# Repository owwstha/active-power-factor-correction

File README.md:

## active power factor correction

### Overview & Objectives

The primary objective was to design a high-efficiency Active Power Factor Correction stage. Utilizing a PI control loop to modulate PWM signals, the system achieves a Power Factor (PF) > 0.99. Key design priorities included:
* Minimizing THD.
* Regulating the DC bus voltage against AC input fluctuations and sudden load transients.

---

### Technical Details

* **Control Architecture**: A dual-loop PI control system manages the feedback: a outer voltage PI loop stabilizes the DC bus output, while a fast inner current PI loop continuously adjusts the duty cycle of the PWM signal.
* **Power Stage**: A diode bridge rectifier converts the AC line voltage to unsmoothed DC, which is immediately fed into a high-frequency Boost Converter. The switched PWM controls the boost stage to shape the input current into a pure sinusoidal waveform aligned with the AC voltage.

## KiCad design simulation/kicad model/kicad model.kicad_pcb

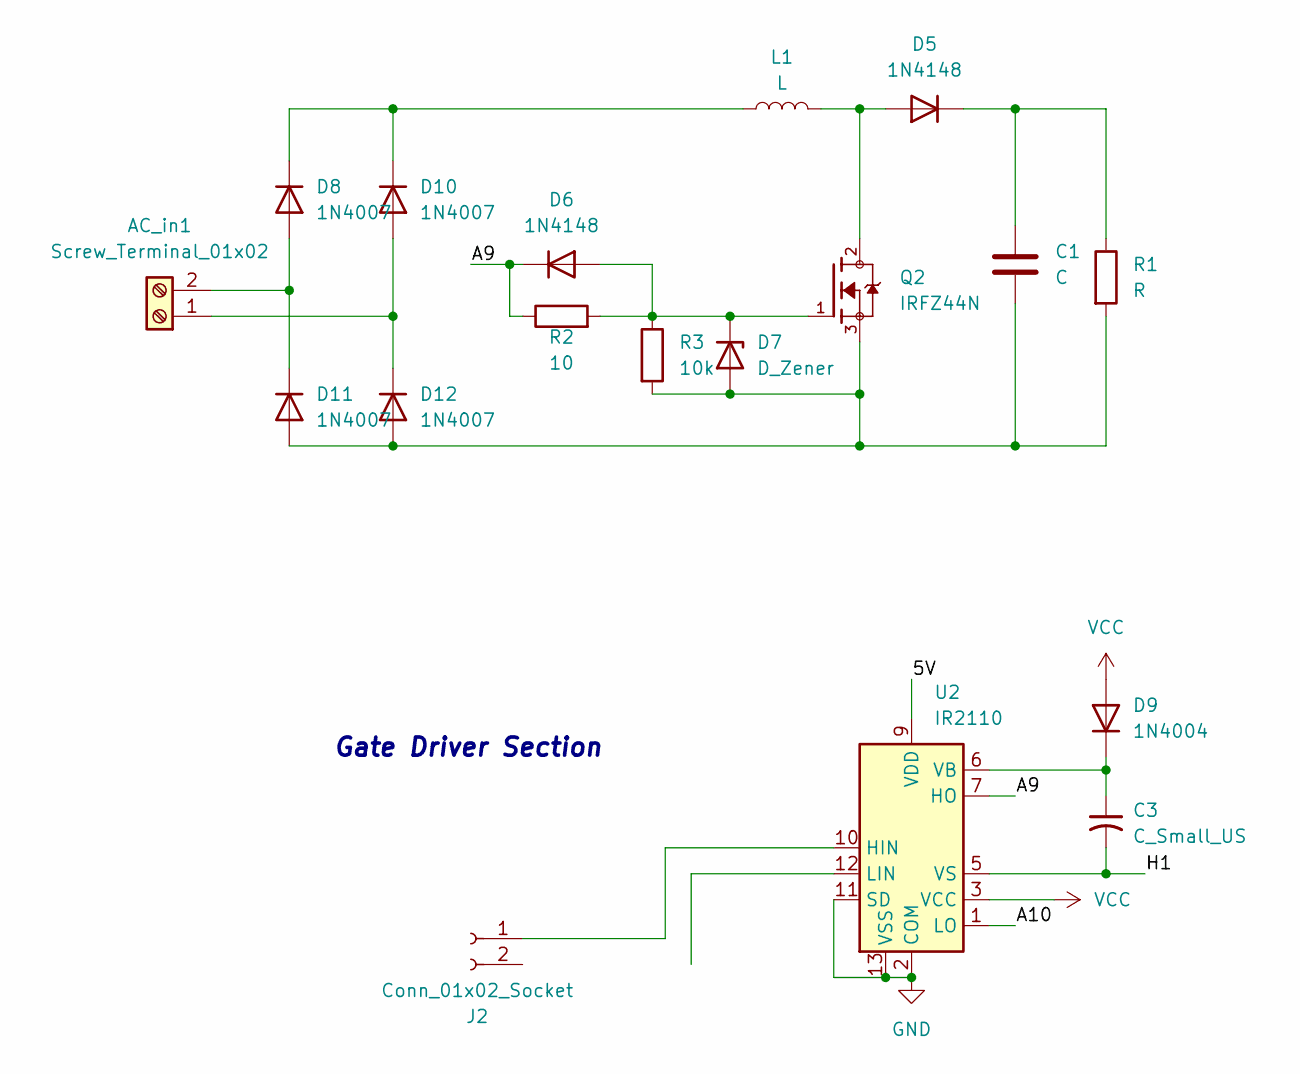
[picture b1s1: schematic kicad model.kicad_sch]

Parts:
AC_in1: Screw_Terminal_01x02; TerminalBlock_Xinya_XY308-2.54-2P_1x02_P2.54mm_Horizontal
C1: C; C_Radial_D6.3mm_H5.0mm_P2.50mm
C3: C_Small_US; C_Radial_D6.3mm_H7.0mm_P2.50mm
D5, D6: 1N4148; D_DO-35_SOD27_P7.62mm_Horizontal
D7: D_Zener; D_A-405_P7.62mm_Horizontal
D8, D10, D11, D12: 1N4007; D_DO-41_SOD81_P10.16mm_Horizontal
D9: 1N4004; D_A-405_P7.62mm_Horizontal
J2: Conn_01x02_Socket; PinHeader_1x01_P2.54mm_Vertical
L1: L; L_Axial_L5.3mm_D2.2mm_P10.16mm_Horizontal_Vishay_IM-1
Q2: IRFZ44N; TO-247-3_Vertical; PARTREV 09/21/10
R1: R; R_Axial_DIN0207_L6.3mm_D2.5mm_P10.16mm_Horizontal
R2: 10; R_Axial_DIN0207_L6.3mm_D2.5mm_P7.62mm_Horizontal
R3: 10k; R_Axial_DIN0207_L6.3mm_D2.5mm_P7.62mm_Horizontal
U2: IR2110; DIP-14_W7.62mm

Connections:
/5V: U2.9 (VDD)
/A9: D6.1 (K), R2.1, U2.7 (HO)
/A10: U2.1 (LO)
/H1: C3.2, U2.5 (VS)
GND: U2.2 (COM), U2.11 (SD), U2.13 (VSS)
unnamed: AC_in1.1, D10.2 (A), D12.1 (K)
unnamed: AC_in1.2, D8.2 (A), D11.1 (K)
unnamed: D5.2 (A), L1.2, Q2.2
unnamed: C1.1, D5.1 (K), R1.1
unnamed: D6.2 (A), D7.1 (K), Q2.1, R2.2, R3.1
unnamed: C3.1, D9.1 (K), U2.6 (VB)
unnamed: D8.1 (K), D10.1 (K), L1.1
unnamed: C1.2, D7.2 (A), D11.2 (A), D12.2 (A), Q2.3, R1.2, R3.2
unnamed: J2.1 (Pin_1_1), U2.10 (HIN)
VCC: D9.2 (A), U2.3 (VCC)

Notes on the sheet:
Gate Driver Section

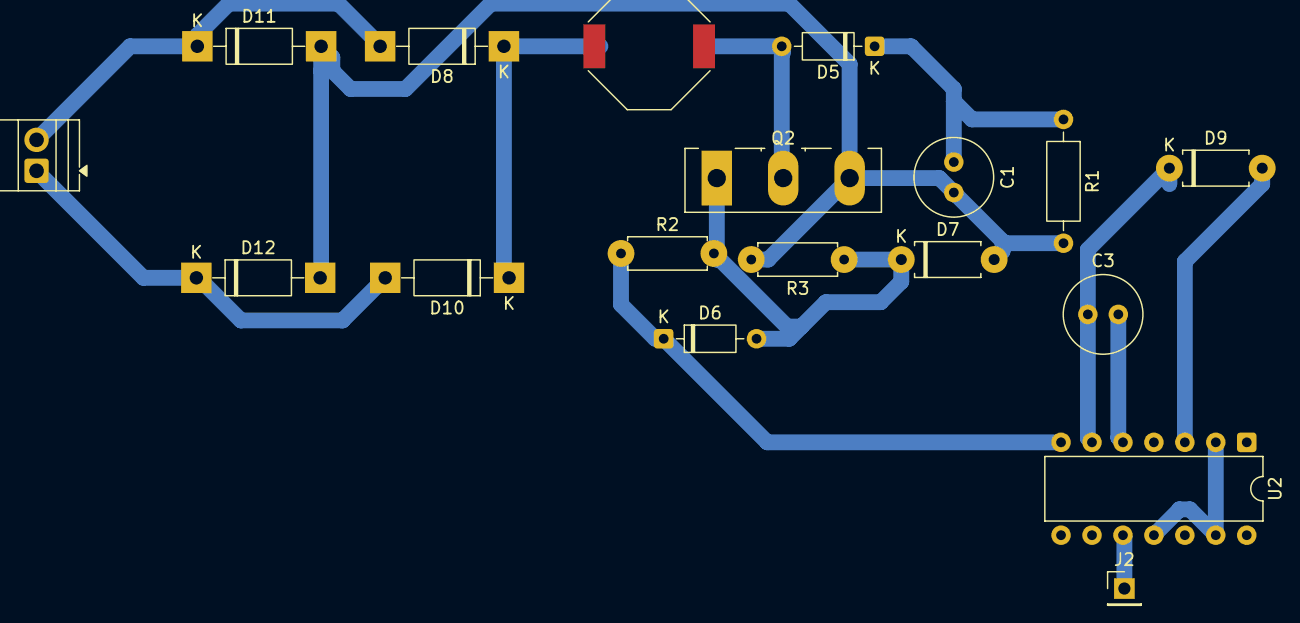
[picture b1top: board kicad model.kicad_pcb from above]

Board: 2 copper layers, 18 parts (0 on the bottom side), 13 nets.
